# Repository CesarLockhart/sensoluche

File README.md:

# sensoluche
Repository for the project with Oscar for a TeadyBear (Peluche) with sensing capabilities for controlling visual applications with enhanced user interaction.

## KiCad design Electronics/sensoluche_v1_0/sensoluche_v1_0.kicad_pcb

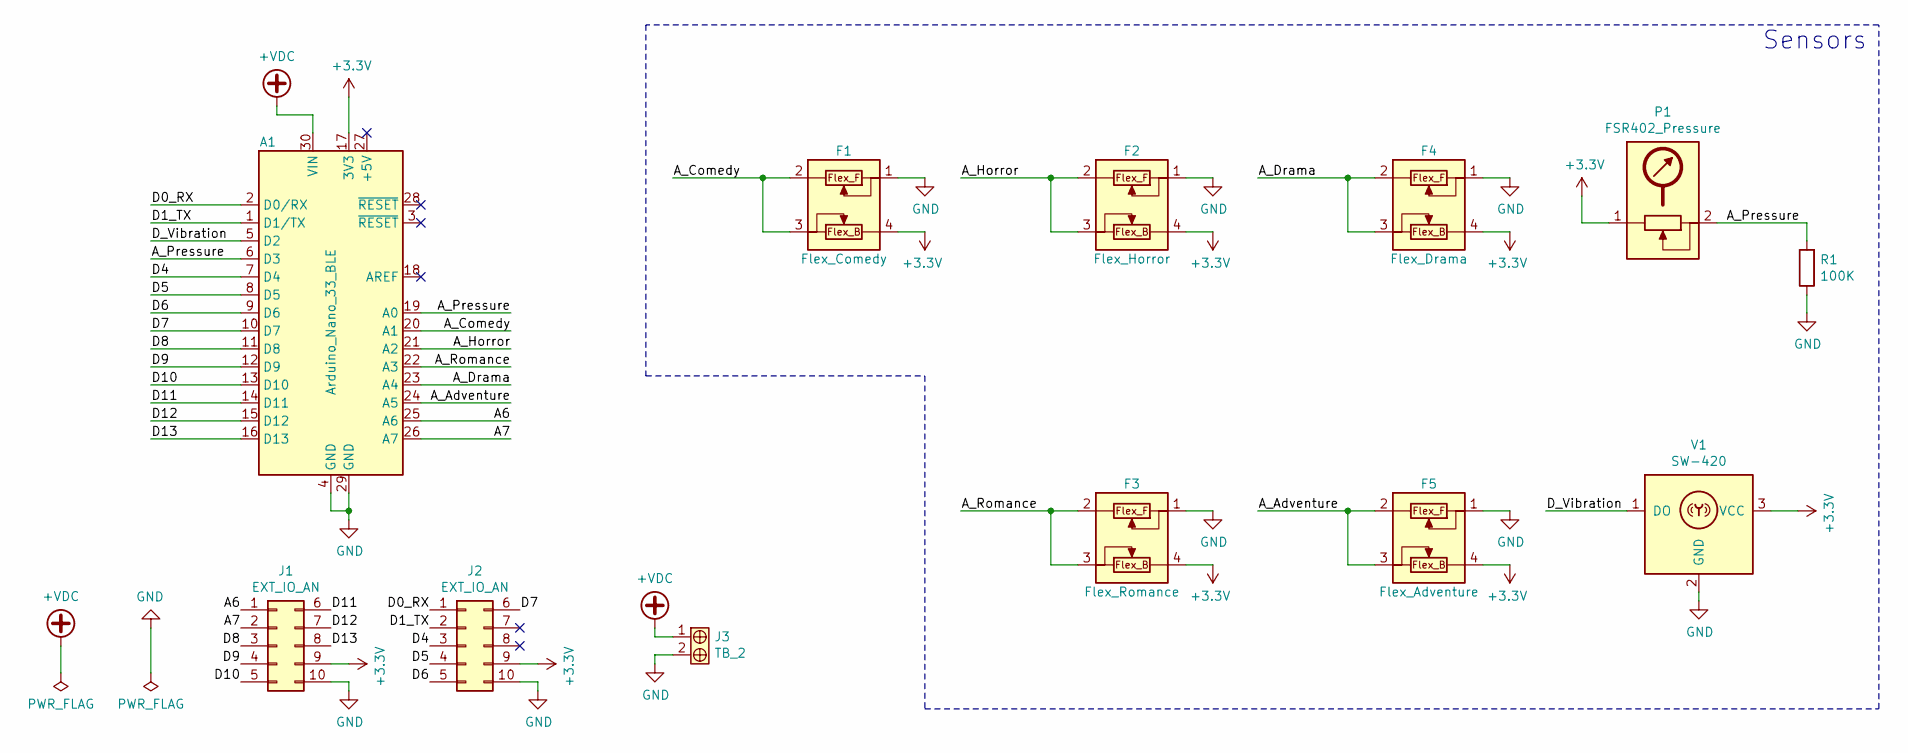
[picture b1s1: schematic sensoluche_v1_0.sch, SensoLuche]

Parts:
A1: Arduino_Nano_33_BLE; Arduino_Nano
F1: Flex_Comedy; TerminalBlock_Phoenix_MPT-0,5-4-2.54_1x04_P2.54mm_Horizontal
F2: Flex_Horror; TerminalBlock_Phoenix_MPT-0,5-4-2.54_1x04_P2.54mm_Horizontal
F3: Flex_Romance; TerminalBlock_Phoenix_MPT-0,5-4-2.54_1x04_P2.54mm_Horizontal
F4: Flex_Drama; TerminalBlock_Phoenix_MPT-0,5-4-2.54_1x04_P2.54mm_Horizontal
F5: Flex_Adventure; TerminalBlock_Phoenix_MPT-0,5-4-2.54_1x04_P2.54mm_Horizontal
J1, J2: EXT_IO_AN; PinHeader_2x05_P2.54mm_Vertical
J3: TB_2; TerminalBlock_Phoenix_MPT-0,5-2-2.54_1x02_P2.54mm_Horizontal
P1: FSR402_Pressure; TerminalBlock_Phoenix_MPT-0,5-2-2.54_1x02_P2.54mm_Horizontal
R1: 100K; R_Axial_DIN0207_L6.3mm_D2.5mm_P7.62mm_Horizontal
V1: SW-420

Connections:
+3V3: A1.17 (3V3), F1.4, F2.4, F3.4, F4.4, F5.4, J1.9, J2.9, P1.1, V1.3 (VCC)
+VDC: A1.30 (VIN), J3.1
/A6: A1.25 (A6), J1.1
/A7: A1.26 (A7), J1.2
/A_Adventure: A1.24 (A5), F5.2, F5.3
/A_Comedy: A1.20 (A1), F1.2, F1.3
/A_Drama: A1.23 (A4), F4.2, F4.3
/A_Horror: A1.21 (A2), F2.2, F2.3
/A_Pressure: A1.6 (D3), A1.19 (A0), P1.2, R1.2
/A_Romance: A1.22 (A3), F3.2, F3.3
/D0_RX: A1.2 (D0/RX), J2.1
/D1_TX: A1.1 (D1/TX), J2.2
/D4: A1.7 (D4), J2.3
/D5: A1.8 (D5), J2.4
/D6: A1.9 (D6), J2.5
/D7: A1.10 (D7), J2.6
/D8: A1.11 (D8), J1.3
/D9: A1.12 (D9), J1.4
/D10: A1.13 (D10), J1.5
/D11: A1.14 (D11), J1.6
/D12: A1.15 (D12), J1.7
/D13: A1.16 (D13), J1.8
/D_Vibration: A1.5 (D2), V1.1 (DO)
GND: A1.4 (GND), A1.29 (GND), F1.1, F2.1, F3.1, F4.1, F5.1, J1.10, J2.10, J3.2, R1.1, V1.2 (GND)

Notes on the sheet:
Sensors

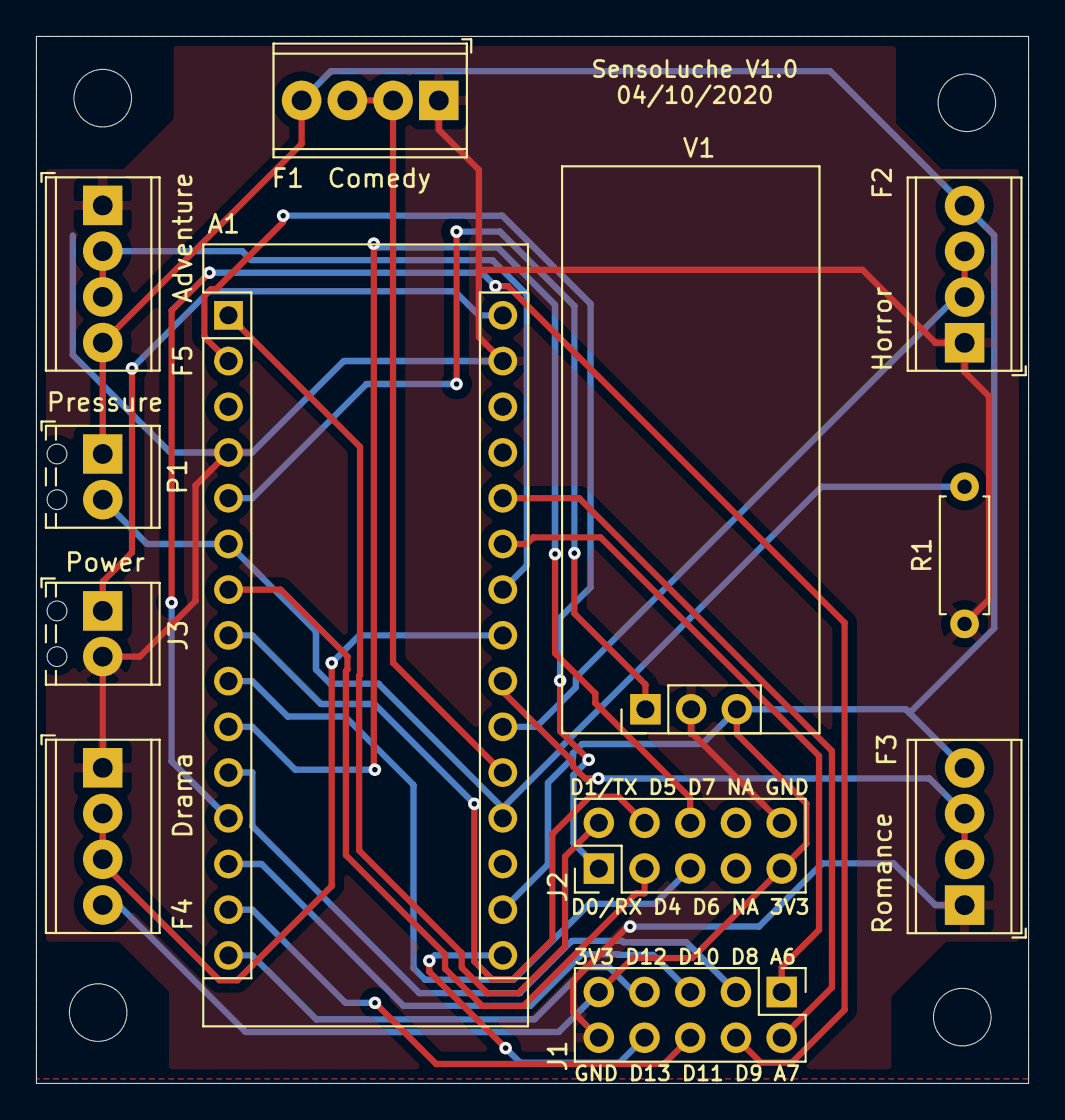
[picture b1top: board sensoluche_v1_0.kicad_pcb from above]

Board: 2 copper layers, 55.1 x 58.2 mm, 16 parts (0 on the bottom side), 24 nets.

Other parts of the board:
BOTTOM_LEFT_HOLE: MountingHole_3.2mm_M3
BOTTOM_RIGTH_HOLE: MountingHole_3.2mm_M3
TOP_LEFT_HOLE: MountingHole_3.2mm_M3
TOP_RIGTH_HOLE: MountingHole_3.2mm_M3

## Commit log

2020-10-02 Testing Repository
2020-10-02 Second Test
2020-10-04 Schematics and PCB finifhed
2020-10-08 V0.1 - Official Version using switches
2020-10-08 V1.0 New flex sensors
2020-10-08 Added the pdf files for printing.
2020-10-09 PCB modifications from Oscar
2020-11-06 Up date to all the files
